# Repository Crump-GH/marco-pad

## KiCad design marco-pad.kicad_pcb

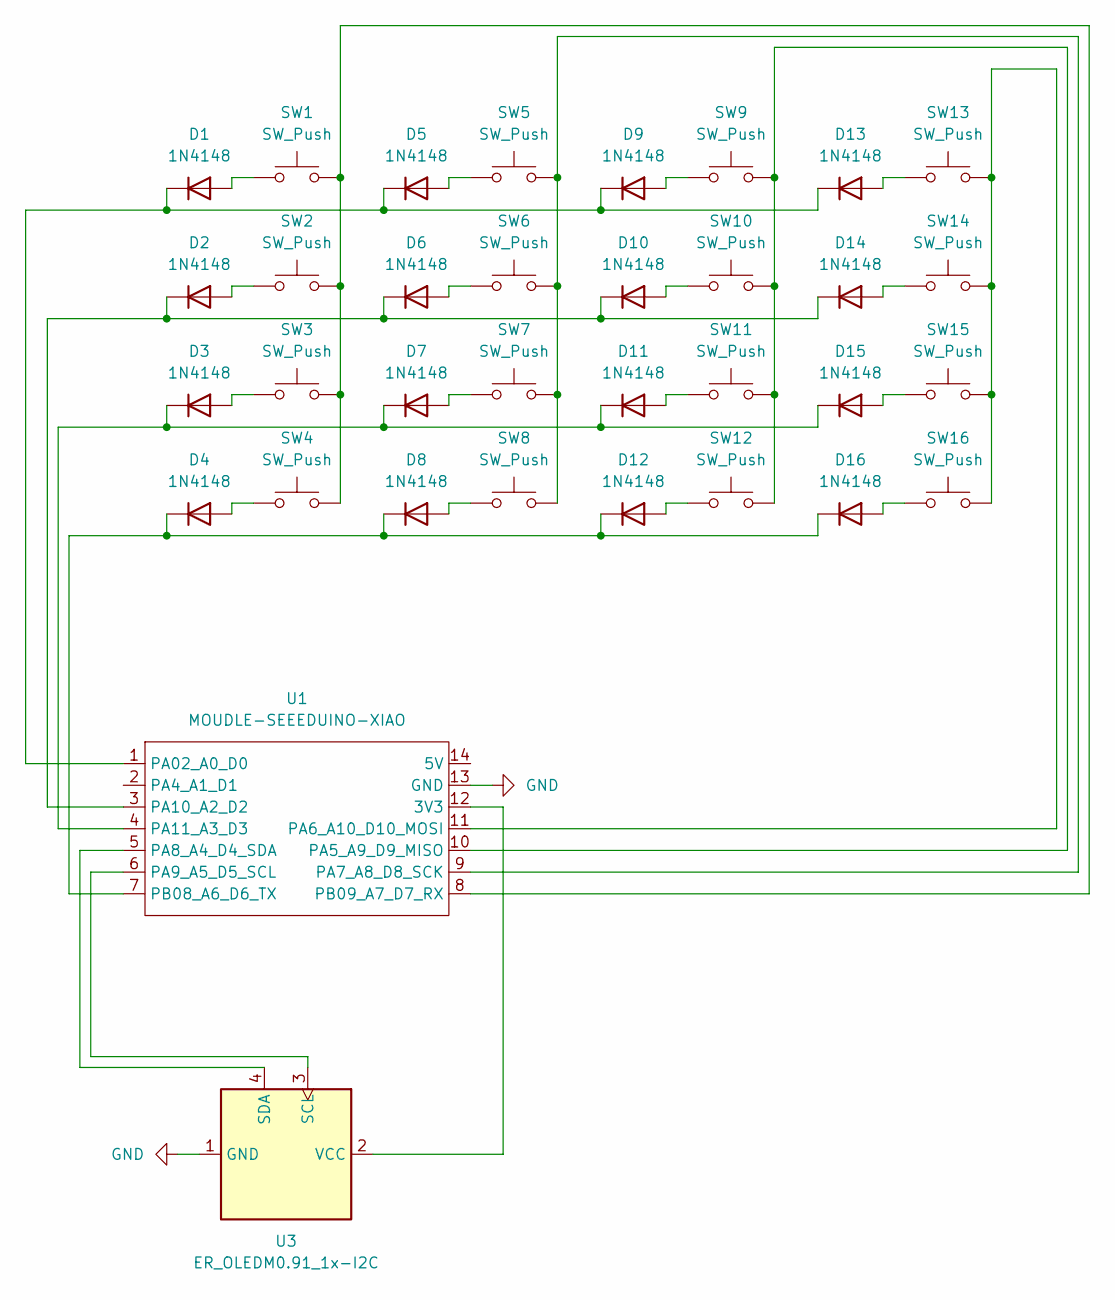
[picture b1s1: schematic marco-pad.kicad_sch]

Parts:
D1, D2, D3, D4, D5, D6, D7, D8, D9, D10, D11, D12, D13, D14, D15, D16: 1N4148; D_DO-35_SOD27_P7.62mm_Horizontal
SW1, SW2, SW3, SW4, SW5, SW6, SW7, SW8, SW9, SW10, SW11, SW12, SW13, SW14, SW15, SW16: SW_Push; SW_Cherry_MX_1.00u_PCB
U1: MOUDLE-SEEEDUINO-XIAO; XIAO-Generic-Hybrid-14P-2.54-21X17.8MM
U3: ER_OLEDM0.91_1x-I2C

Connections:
GND: U1.13 (GND), U3.1 (GND)
unnamed: D1.2 (A), SW1.1
unnamed: D1.1 (K), D5.1 (K), D9.1 (K), D13.1 (K), U1.1 (PA02_A0_D0)
unnamed: D2.2 (A), SW2.1
unnamed: D3.2 (A), SW3.1
unnamed: D4.2 (A), SW4.1
unnamed: D5.2 (A), SW5.1
unnamed: D6.2 (A), SW6.1
unnamed: D7.2 (A), SW7.1
unnamed: D8.2 (A), SW8.1
unnamed: D9.2 (A), SW9.1
unnamed: D10.2 (A), SW10.1
unnamed: D2.1 (K), D6.1 (K), D10.1 (K), D14.1 (K), U1.3 (PA10_A2_D2)
unnamed: D11.2 (A), SW11.1
unnamed: D3.1 (K), D7.1 (K), D11.1 (K), D15.1 (K), U1.4 (PA11_A3_D3)
unnamed: D12.2 (A), SW12.1
unnamed: D4.1 (K), D8.1 (K), D12.1 (K), D16.1 (K), U1.7 (PB08_A6_D6_TX)
unnamed: D13.2 (A), SW13.1
unnamed: D14.2 (A), SW14.1
unnamed: D15.2 (A), SW15.1
unnamed: D16.2 (A), SW16.1
unnamed: U1.12 (3V3), U3.2 (VCC)
unnamed: SW9.2, SW10.2, SW11.2, SW12.2, U1.10 (PA5_A9_D9_MISO)
unnamed: SW13.2, SW14.2, SW15.2, SW16.2, U1.11 (PA6_A10_D10_MOSI)
unnamed: SW5.2, SW6.2, SW7.2, SW8.2, U1.9 (PA7_A8_D8_SCK)
unnamed: U1.5 (PA8_A4_D4_SDA), U3.4 (SDA)
unnamed: U1.6 (PA9_A5_D5_SCL), U3.3 (SCL)
unnamed: SW1.2, SW2.2, SW3.2, SW4.2, U1.8 (PB09_A7_D7_RX)

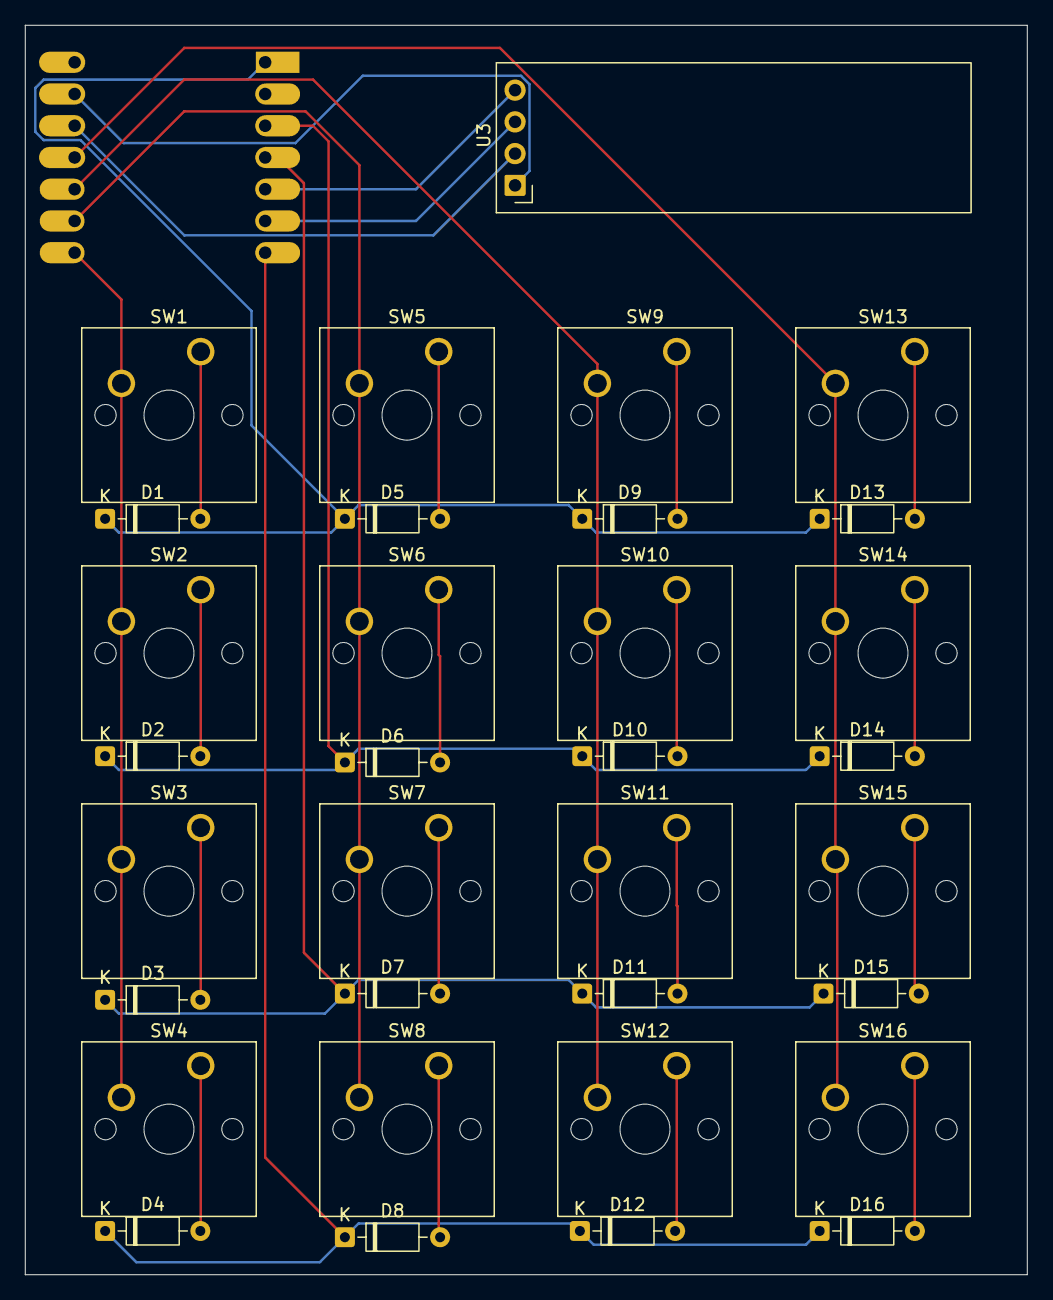
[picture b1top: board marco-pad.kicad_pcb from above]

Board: 2 copper layers, 80.2 x 100.0 mm, 34 parts (1 on the bottom side), 28 nets.

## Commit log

2026-06-02 schenatic and PCB done
2026-06-02 Added Gerber files
